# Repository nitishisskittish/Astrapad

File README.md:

## **Astrapad**
---
A 7 key macropad with a rotary encoder, OLED screen, and 16 WS2812B LED’s. Currently runs on KMK firmware

### **Features**
---
- Two Piece 3D Printable Case
- 128x32 OLED Display
- EC11 Rotary encoder
- 16 WS2812B RGB LEDs, probably waaayyy too much, but the more the merrier I guess
- 7 Keys

### **CAD Model**
---
The case is held together by 4 M3 Bolts and heatset inserts, 1 in each corner. The bottom half of the case has a built in tilt. Originally I designed this with see-through plastic “windows” in mind, but as of now those windows have been replaced with direct holes looking into the PCB. Maybe I’ll add them later.

### **PCB**
---
I made my PCB in KiCad. I got the bangboo silkscreen arts from the [Zenless Zone Zero Fandom Sticker Page](https://zenless-zone-zero.fandom.com/wiki/Stickers), and the pikachu art from [pixlecheese](https://www.pixilart.com/art/pikachu-thunderbolt-1a236168d6612c3)

- Schematic:

- Schematic:

- My favorite part of the whole project tbh, made me feel very smart. Also if you're interested the numbers at the very bottom are binary, although it doesn’t spell out anything that interesting

### **Firmware**
---
Currently Astrapad runs on KMK, but I plan on switching to QMK later because I want to add [VIA](https://caniusevia.com/) support
- The rotary encoder changes the volume, and you can tap it to toggle mute
- The top left and top right keys skips forward or backward respectively in the playback queue
- The top middle button and bottom 3 buttons act as WASD keys, with the top middle button being the W Key
- The bottom right button is currently mapped to a custom shortcut I have on my computer that opens Spotify
- The OLED Screen displays the current volume level of whatever device the macropad is currently connected to
- I have a list of features I want to add commented in the KMK main.py file if you're interested in that
### **BOM**
---
- 1x Seeed XIAO RP2040
- 1x 0.91 inch OLED displays 
- 1x EC11 rotary encoders
- 1x Case (2 3D printed parts)
- 1x 3D printed EC11 (Rotary Encoder) Knob
- 4x M3x5x4 Heatset inserts
- 4x M3x16mm screws
- 7x Cherry MX Switches
- 7x DSA keycaps
- 8x Through-hole 1N4148 Diodes
- 16x SK6812 MINI-E LEDs

### **Extra Stuff**
---
The example I’m basing this README off of had this section, so I’m adding it too. 
Thanks a lot to the Blueprint Hackclub slack, I probably wouldn’t have finished this project without their help.
Ummm yeah, that’s it I guess.

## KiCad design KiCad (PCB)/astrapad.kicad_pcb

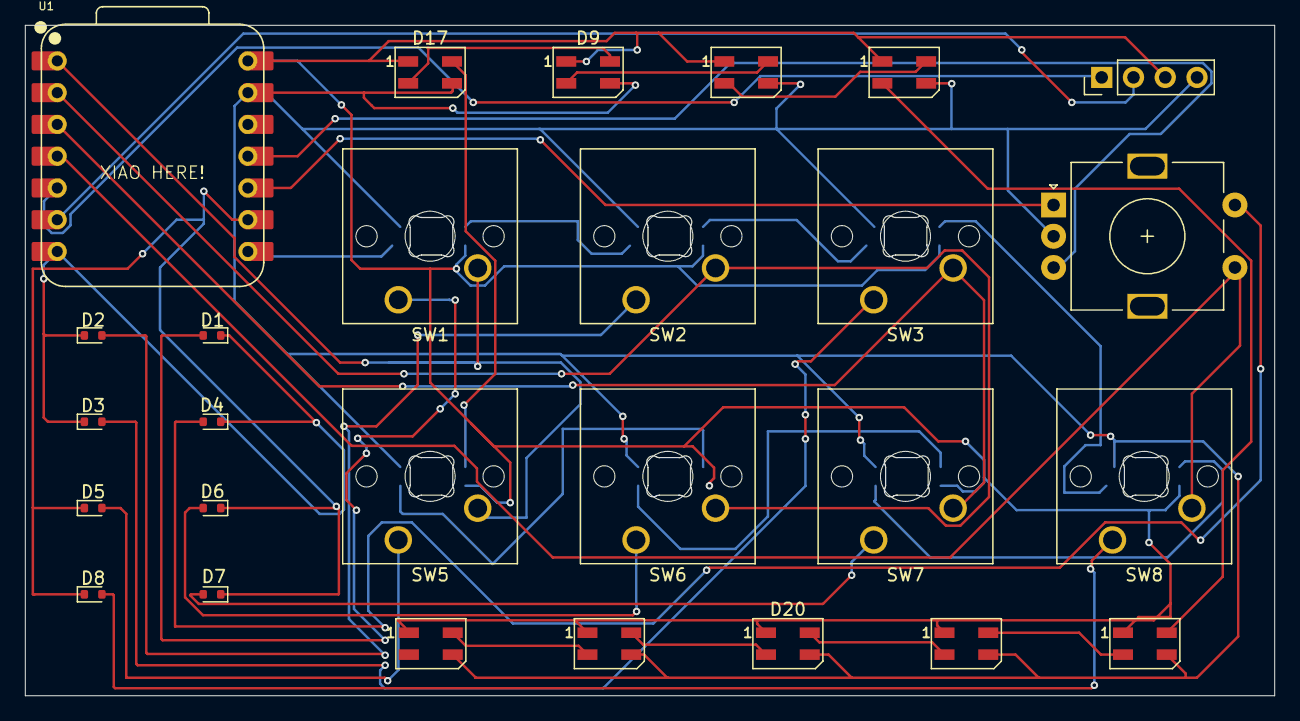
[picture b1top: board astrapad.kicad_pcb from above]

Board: 2 copper layers, 99.9 x 53.6 mm, 34 parts (0 on the bottom side), 36 nets.

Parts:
D1, D2, D3, D4, D5, D6, D7, D8: 1N4148WT; D_SOD-523
D9, D17, D18, D19, D20, D22, D23, D24, D25: WS2812B; LED_SK6812MINI_PLCC4_3.5x3.5mm_P1.75mm
D10, D11, D12, D13, D14, D15, D16: WS2812B; MX_SK6812MINI-E_REV
J1: OLED_DISPLAY; PinHeader_1x04_P2.54mm_Vertical
SW1, SW2, SW3, SW5, SW6, SW7, SW8: SW_Push; SW_Cherry_MX_1.00u_PCB
SW13: RotaryEncoder_Switch; RotaryEncoder_Alps_EC11E-Switch_Vertical_H20mm
U1: XIAO-RP2040-DIP

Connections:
+5V: D9.1 (VDD), D10.1 (VDD), D11.1 (VDD), D12.1 (VDD), D13.1 (VDD), D14.1 (VDD), D15.1 (VDD), D16.1 (VDD), D17.1 (VDD), D18.1 (VDD), D19.1 (VDD), D20.1 (VDD), D22.1 (VDD), D23.1 (VDD), D24.1 (VDD), D25.1 (VDD), J1.3, U1.14 (VBUS)
Column 1: SW1.2, SW5.2, U1.1 (GPIO26/ADC0/A0)
Column 2: SW2.2, SW6.2, U1.2 (GPIO27/ADC1/A1)
Column 3: SW3.2, SW7.2, U1.3 (GPIO28/ADC2/A2)
Column 4: SW8.2, SW13.S1, U1.4 (GPIO29/ADC3/A3)
GND: D9.3 (VSS), D10.3 (VSS), D11.3 (VSS), D12.3 (VSS), D13.3 (VSS), D14.3 (VSS), D15.3 (VSS), D16.3 (VSS), D17.3 (VSS), D18.3 (VSS), D19.3 (VSS), D20.3 (VSS), D22.3 (VSS), D23.3 (VSS), D24.3 (VSS), D25.3 (VSS), J1.4, SW13.C, U1.13 (GND)
unnamed: D1.2 (A), SW1.1
unnamed: D2.2 (A), SW2.1
unnamed: D3.2 (A), SW3.1
unnamed: D4.2 (A), SW13.S2
unnamed: D5.2 (A), SW5.1
unnamed: D6.2 (A), SW6.1
unnamed: D7.2 (A), SW7.1
unnamed: D8.2 (A), SW8.1
unnamed: D10.4 (DIN), U1.8 (GPIO1/RX)
unnamed: D10.2 (DOUT), D11.4 (DIN)
unnamed: D11.2 (DOUT), D12.4 (DIN)
unnamed: D12.2 (DOUT), D13.4 (DIN)
unnamed: D13.2 (DOUT), D14.4 (DIN)
unnamed: D14.2 (DOUT), D15.4 (DIN)
unnamed: D15.2 (DOUT), D16.4 (DIN)
unnamed: D16.2 (DOUT), D17.4 (DIN)
unnamed: D9.4 (DIN), D17.2 (DOUT)
unnamed: D9.2 (DOUT), D18.4 (DIN)
unnamed: D18.2 (DOUT), D19.4 (DIN)
unnamed: D19.2 (DOUT), D22.4 (DIN)
unnamed: D20.4 (DIN), D23.2 (DOUT)
unnamed: D20.2 (DOUT), D24.4 (DIN)
unnamed: D22.2 (DOUT), D23.4 (DIN)
unnamed: D24.2 (DOUT), D25.4 (DIN)
Rotary A: SW13.A, U1.10 (GPIO4/MISO)
Rotary B: SW13.B, U1.11 (GPIO3/MOSI)
Row 1: D1.1 (K), D2.1 (K), D3.1 (K), D4.1 (K), U1.7 (GPIO0/TX)
Row 2: D5.1 (K), D6.1 (K), D7.1 (K), D8.1 (K), U1.9 (GPIO2/SCK)
SCL: J1.2, U1.6 (GPIO7/SCL)
SDA: J1.1, U1.5 (GPIO6/SDA)

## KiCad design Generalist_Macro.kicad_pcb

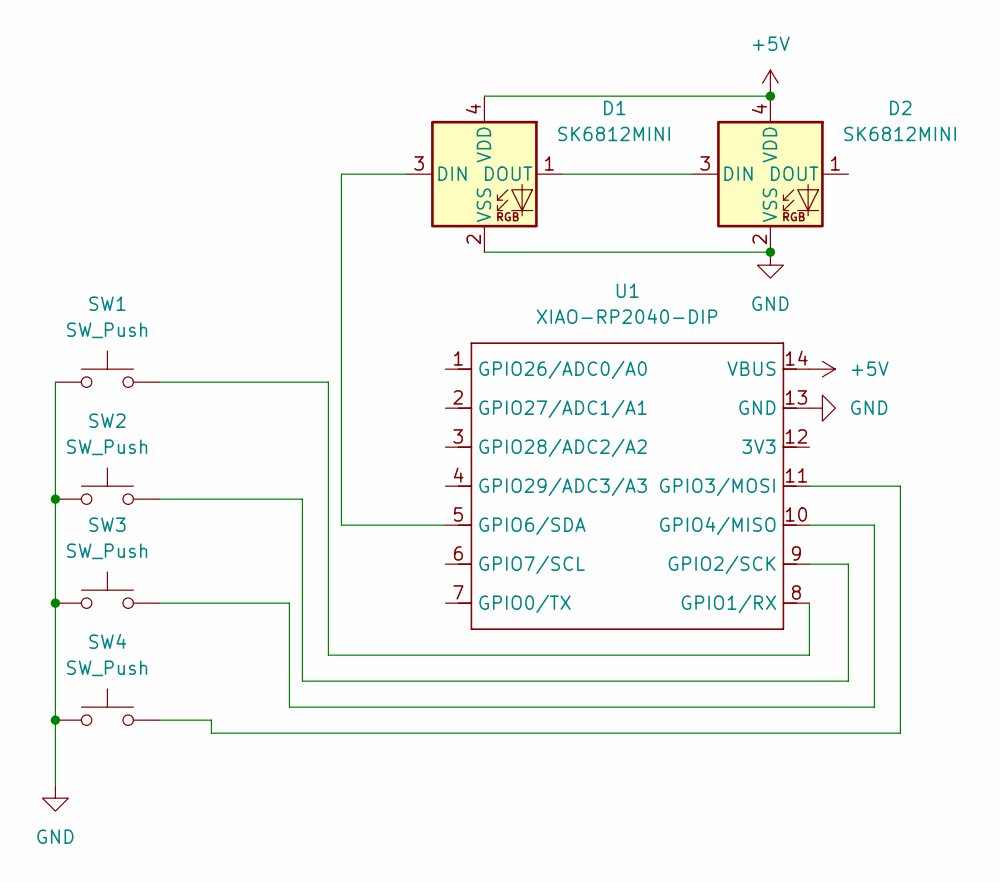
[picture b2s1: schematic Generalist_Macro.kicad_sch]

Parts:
D1, D2: SK6812MINI; LED_SK6812MINI_PLCC4_3.5x3.5mm_P1.75mm
SW1, SW2, SW3, SW4: SW_Push; SW_Cherry_MX_1.00u_PCB
U1: XIAO-RP2040-DIP

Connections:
+5V: D1.4 (VDD), D2.4 (VDD), U1.14 (VBUS)
GND: D1.2 (VSS), D2.2 (VSS), SW1.1, SW2.1, SW3.1, SW4.1, U1.13 (GND)
unnamed: D1.3 (DIN), U1.5 (GPIO6/SDA)
unnamed: D1.1 (DOUT), D2.3 (DIN)
unnamed: SW1.2, U1.8 (GPIO1/RX)
unnamed: SW2.2, U1.9 (GPIO2/SCK)
unnamed: SW4.2, U1.11 (GPIO3/MOSI)
unnamed: SW3.2, U1.10 (GPIO4/MISO)

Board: 2 copper layers, 7 parts (0 on the bottom side), 8 nets, no tracks yet.

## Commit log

2025-11-28 Blueprint HackClub Macro Project - Initial Commit
2025-12-04 Renamed Project. Reorganized files. Cleaned up routing Struggled with importing 3D model of PCB with Components for hours on end. THE SEEED CONTROLLER STILL DOESNT SHOW UP IN 3D VIEW. gave up. I WILL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
2025-12-07 Resized PCB to fit 100mmx100mm limit Turns out the PCB has a max size of 100mmx100mm, mine was 106x59. I resized it though so we good now
2025-12-08 Finished Firmware
2025-12-20 Syncing PCB 3D Model
2025-12-22 Added some silkscreens
2025-12-22 Forgot to export updated 3d model
2025-12-22 Didn't update 3D Model paths after changing file organization
2025-12-22 Syncing Desktop
2025-12-22 Reorganized Images
2025-12-22 README Completed, Submitting for Review
    Updated README to improve clarity and formatting.
2025-12-22 Forgot to describe display function
2025-12-23 PCB image in readme had wrong silkscreens
2025-12-23 Grammar Correction
2025-12-23 Added Pikachu silkscreen art to pcb, exported Gerber files
2026-04-09 So...it's been a while A lot of things went wrong with assembly, just to name a few: The 3D printed case was to tight, and the pcb didn't fit inside The upwards facing LED's were impossible to solder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
    Until now,
    With this new firmware the macropad now works. Buttons (well only one right now, haven't given the rest a function), rotary dial, the screen, the LEDs backlighting the keys, all of it.
    It did take me a while to find time, but I think I can now say that this project wasn't a complete fai
2026-04-22 Some small changes to the screen Also I may have forgotten to actually update the firmware in my project folder that I sync with github, I only changed the actual firmware saved to the macropad itsel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
